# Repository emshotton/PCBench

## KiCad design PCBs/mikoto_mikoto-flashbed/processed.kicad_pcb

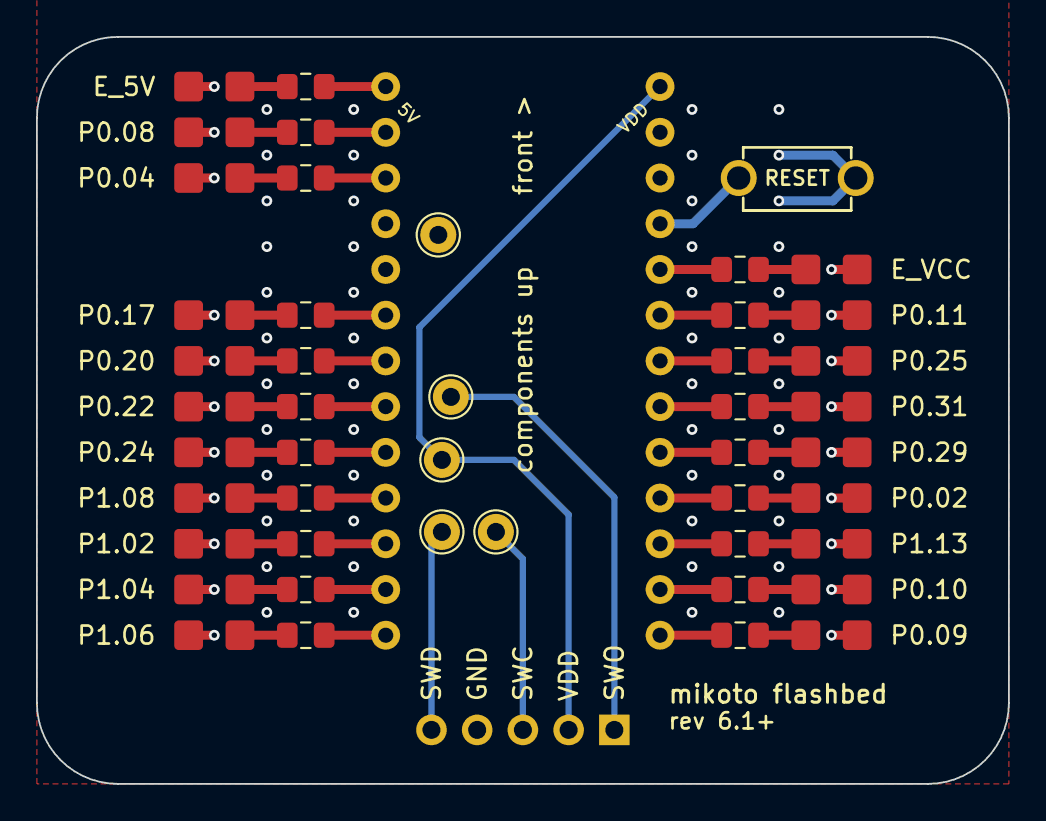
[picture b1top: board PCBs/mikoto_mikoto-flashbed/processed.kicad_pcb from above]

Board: 2 copper layers, 54.0 x 41.5 mm, 48 parts (1 on the bottom side), 46 nets.

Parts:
D1, D2, D3, D4, D5, D6, D7, D8, D9, D10, D11, D12, D13, D14, D15, D16, D17, D18, D19, D20: LED_Small; LED_1206_3216M_Castellated-nosilk
J1, J2, J3, J4, J5: Conn_01x01; TestPoint_THTPad_D2.0mm_Drill1.0mm
J7: Conn_01x05; PinHeader_1x05_P2.54mm_Horizontal
R1, R2, R3, R4, R5, R6, R7, R8, R9, R10, R11, R12, R13, R14, R15, R16, R17, R18, R19, R20: 2.2k; R_0805_2012Metric_Pad1.15x1.40mm_HandSolder
SW1: TVBP06; TACT_SWITCH_TVBP06
U1: mikoto-pins

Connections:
EXT_5V: R1.1, U1.1 (EXT_5V)
EXT_VCC: R20.1, U1.22 (VCC)
GND: D1.1 (K), D2.1 (K), D3.1 (K), D4.1 (K), D5.1 (K), D6.1 (K), D7.1 (K), D8.1 (K), D9.1 (K), D10.1 (K), D11.1 (K), D12.1 (K), D13.1 (K), D14.1 (K), D15.1 (K), D16.1 (K), D17.1 (K), D18.1 (K), D19.1 (K), D20.1 (K), J2.1, J7.4, SW1.2, U1.4 (GND), U1.5 (GND), U1.24 (GND)
unnamed: D1.2 (A), R1.2
unnamed: D2.2 (A), R2.2
unnamed: D3.2 (A), R3.2
unnamed: D4.2 (A), R4.2
unnamed: D5.2 (A), R5.2
unnamed: D6.2 (A), R6.2
unnamed: D7.2 (A), R7.2
unnamed: D8.2 (A), R8.2
unnamed: D9.2 (A), R9.2
unnamed: D10.2 (A), R10.2
unnamed: D11.2 (A), R11.2
unnamed: D12.2 (A), R12.2
unnamed: D13.2 (A), R13.2
unnamed: D14.2 (A), R14.2
unnamed: D15.2 (A), R15.2
unnamed: D16.2 (A), R16.2
unnamed: D17.2 (A), R17.2
unnamed: D18.2 (A), R18.2
unnamed: D19.2 (A), R19.2
unnamed: D20.2 (A), R20.2
P0.02: R15.1, U1.17
P0.04: R3.1, U1.3
P0.08: R2.1, U1.2
P0.09: R12.1, U1.14
P0.10: R13.1, U1.15
P0.11: R19.1, U1.21
P0.17: R4.1, U1.6
P0.20: R5.1, U1.7
P0.22: R6.1, U1.8
P0.24: R7.1, U1.9
P0.25: R18.1, U1.20
P0.29: R16.1, U1.18
P0.31: R17.1, U1.19
P1.02: R9.1, U1.11
P1.04: R10.1, U1.12
P1.06: R11.1, U1.13
P1.08: R8.1, U1.10
P1.13: R14.1, U1.16
RESET: SW1.1, U1.23 (RST)
SWC: J3.1, J7.3
SWD: J1.1, J7.5
SWO: J5.1, J7.1
VDD: J4.1, J7.2, U1.26 (VDD)

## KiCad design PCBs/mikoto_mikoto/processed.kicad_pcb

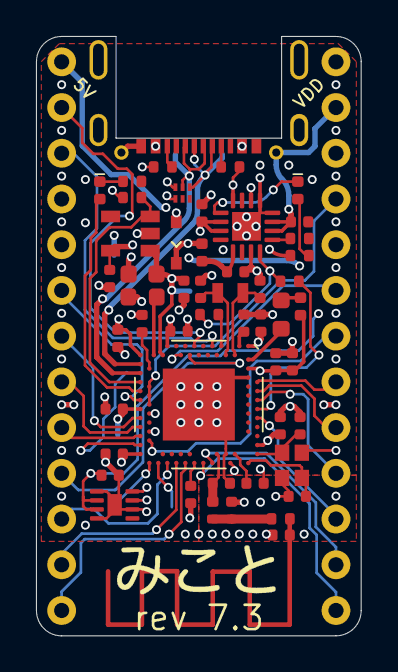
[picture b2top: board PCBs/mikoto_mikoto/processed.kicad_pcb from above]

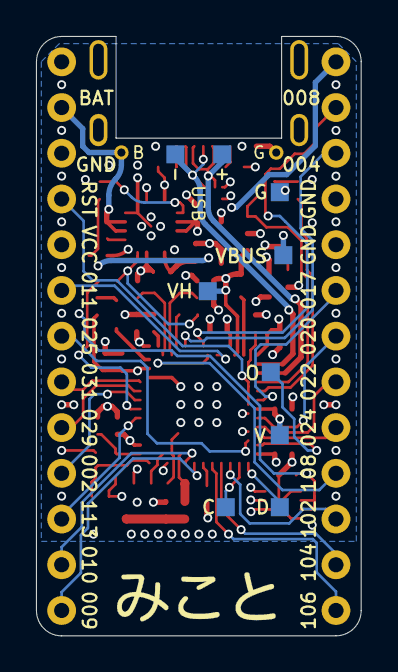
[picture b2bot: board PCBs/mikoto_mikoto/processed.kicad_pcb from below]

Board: 4 copper layers, 18.0 x 33.3 mm, 67 parts (10 on the bottom side), 61 nets.

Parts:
AE1: Antenna; 2.4GHz-meander-antenna-v2
C1, C13, C14, C20, C24, C25, C26: 4.7uF; Capacitor_0402_1005M-nosilk
C2, C3, C4, C10, C19: 100nF; Capacitor_0402_1005M-nosilk
C5, C9: 1pF; Capacitor_0402_1005M-nosilk
C6, C7, C17, C18: 15pF; Capacitor_0402_1005M-nosilk
C8, C15, C23: 1uF; Capacitor_0402_1005M-nosilk
C11: 100pF; Capacitor_0402_1005M-nosilk
C12: 1nF; Capacitor_0402_1005M-nosilk
C16: 47nF; Capacitor_0402_1005M-nosilk
C21: 10uF; Capacitor_0603_1608M-nosilk
C22: 1.5pF; Capacitor_0402_1005M-nosilk
D1: BLUE; LED_0402_1005Metric-nosilk
D3: ORANGE; LED_0402_1005Metric-nosilk
D5: PMEG4010CEJ; D_SOD-323F-nosilk
DUMMY1: logo_front; mikoto-logo
DUMMY2: logo_back; mikoto-logo
F1: 500mA hold; Fuse_0402_1005Metric
J1: USB_C_Receptacle_USB2.0; USB-C_C168688
J4, J5: PTH; PTH-0.8_0.45mm
L1: 3.9nH; Inductor_0402_1005M-nosilk
L2: 15nH; Inductor_0402_1005M-nosilk
L3, L4: 10uH; Inductor_0603_1608M-nosilk
NT1: NetTie_2; net-tie-2-tiny
R1: 3.9k; Resistor_0402_1005M-nosilk
R2: 2M; Resistor_0402_1005M-nosilk
R5: 1.5k; Resistor_0402_1005M-nosilk
R6, R7, R8: 10k; Resistor_0402_1005M-nosilk
R9, R10: 5.1k; Resistor_0402_1005M-nosilk
R11: 0R; Resistor_0402_1005M-nosilk
TP1, TP2, TP3, TP4, TP5, TP6, TP7, TP8, TP9: PAD; TestPoint_Pad_1.0x1.0mm-nosilk
U1: nRF52840; AQFN-73-1EP_7x7mm_P0.5mm_NRF52840-custom
U2: BQ24075RGT; VQFN-16-1EP_3x3mm_P0.5mm_EP1.6x1.6mm
U3: XC6220B331MR; SOT-23-5
U4: mikoto-pins
U5: ESDR0502NMUTAG; UDFN-6_1.2x1.0mm_P0.4mm
U6: MAX17048; TDFN-8-1EP_2x2mm_P0.5mm_EP0.8x1.2mm
Y1: 32MHz; Crystal_SMD_2016-4Pin_2.0x1.6mm
Y2: 32.768 kHz; Crystal_SMD_2012-2Pin_2.0x1.2mm

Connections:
/ANT: AE1.1 (A), C22.2, R11.2
/CC1: J1.A5 (CC1), R9.1
/CC2: J1.B5 (CC2), R10.1
BAT_I2C_SCL: U1.AC15 (P0.19), U6.7 (SCL)
BAT_I2C_SDA: U1.AC19 (P0.23), U6.8 (SDA)
BLUE_LED: D1.2 (A), U1.AD10 (P0.15)
CHARGE_CTRL_1: R7.1, U1.G1 (P0.26)
CHARGE_CTRL_2: R1.2, U1.A14 (P1.15)
EXT_5V: D5.1 (K), F1.2, U4.1 (EXT_5V)
GND: C1.1, C2.1, C3.1, C4.1, C5.1, C6.2, C7.2, C8.1, C10.2, C11.2, C12.2, C13.2, C14.1, C15.1, C16.1, C17.1, C18.1, C19.1, C20.1, C21.1, C22.1, C23.2, C24.1, C25.1, C26.1, J1.A1 (GND), J5.1, NT1.2, R2.2, R5.1, R8.2, R9.2, R10.2, TP5.1, U1.B7 (VSS), U1.EP (VSS), U2.4 (~CE), U2.5 (EN2), U2.8 (VSS), U2.15 (SYSOFF), U2.17 (VSS), U3.2 (GND), U4.4 (GND), U4.5 (GND), U4.24 (GND), U5.1 (GND), U6.1 (CTG), U6.4 (GND), U6.6 (QSTRT), U6.9 (EP), Y1.2, Y1.4
unnamed: C5.2, L1.1, R11.1
unnamed: D1.1 (K), R5.2
unnamed: D3.2 (A), R6.2
unnamed: D3.1 (K), U2.9 (~CHG)
unnamed: L2.2, L3.1
unnamed: C9.2, L1.2, U1.H23 (ANT)
unnamed: L3.2, U1.B3 (DCC)
unnamed: L4.2, U1.AB2 (DCCH)
unnamed: C10.1, U1.C1 (DEC1)
unnamed: C11.1, U1.D23 (DEC3)
unnamed: C15.2, C16.2, L2.1, U1.B5 (DEC4), U1.E24 (DEC6)
unnamed: C12.1, U1.N24 (DEC5)
unnamed: C13.1, U1.AC5 (DECUSB)
unnamed: C6.1, U1.B24 (XC1), Y1.1
unnamed: C7.1, U1.A23 (XC2), Y1.3
unnamed: C17.2, U1.D2 (XL1/P0.00), Y2.1
unnamed: C18.2, U1.F2 (XL2/P0.01), Y2.2
unnamed: C23.1, F1.1, U2.13 (IN)
unnamed: R1.1, R7.2, U2.16 (ISET)
unnamed: R8.1, U2.1 (TS)
P0.02: U1.A12 (AIN0/P0.02), U4.17
P0.04: U1.J1 (AIN2/P0.04), U4.3
P0.08: U1.N1 (P0.08), U4.2
P0.09: U1.L24 (NFC1/P0.09), U4.14
P0.10: U1.J24 (NFC2/P0.10), U4.15
P0.11: U1.T2 (TRACEDATA2/P0.11), U4.21
P0.17: U1.AD12 (P0.17), U4.6
P0.20: U1.AD16 (P0.20), U4.7
P0.22: U1.AD18 (P0.22), U4.8
P0.24: U1.AD20 (P0.24), U4.9
P0.25: U1.AC21 (P0.25), U4.20
P0.29: U1.A10 (AIN5/P0.29), U4.18
P0.31: U1.A8 (AIN7/P0.31), U4.19
P1.02: U1.W24 (P1.02), U4.11
P1.04: U1.U24 (P1.04), U4.12
P1.06: U1.R24 (P1.06), U4.13
P1.08: U1.P2 (P1.08), U4.10
P1.13: U1.A16 (P1.13), U4.16
PPH_VCC: C20.2, U3.5 (VOUT), U4.22 (VCC)
PPH_VCC_CTRL: R2.1, U1.AD8 (P0.13), U3.3 (CE)
RESET: U1.AC9 (P0.14), U1.AC11 (P0.16), U1.AC13 (P0.18/~RESET), U4.23 (RST)
SWC: TP1.1, U1.AA24 (SWDCLK)
SWD: TP2.1, U1.AC24 (SWDIO)
SWO: TP9.1, U1.AD22 (TRACEDATA0/P1.00)
USB_D+: J1.A6 (D+), J1.B6 (D+), TP6.1, U1.AD6 (D+), U5.5 (D+)
USB_D-: J1.A7 (D-), J1.B7 (D-), TP4.1, U1.AD4 (D-), U5.4 (D-)
VBAT: C19.2, C26.2, J4.1, U2.2 (BAT), U2.3 (BAT), U4.25 (RAW), U6.2 (CELL), U6.3 (VDD)
VBUS: C14.2, D5.2 (A), J1.A4 (VBUS), TP8.1, U1.AD2 (VBUS), U5.6 (VBUS)
VDDH: C21.2, C24.2, C25.2, R6.1, TP7.1, U1.Y2 (VDDH), U2.6 (EN1), U2.10 (OUT), U2.11 (OUT), U3.1 (VIN)
VDD_NRF: C1.2, C2.2, C3.2, C4.2, C8.2, L4.1, TP3.1, U1.A22 (VDD), U1.AD14 (VDD), U1.AD23 (VDD), U1.B1 (VDD), U1.W1 (VDD), U4.26 (VDD)
VSS_PA: C9.1, NT1.1, U1.F23 (VSS_PA)

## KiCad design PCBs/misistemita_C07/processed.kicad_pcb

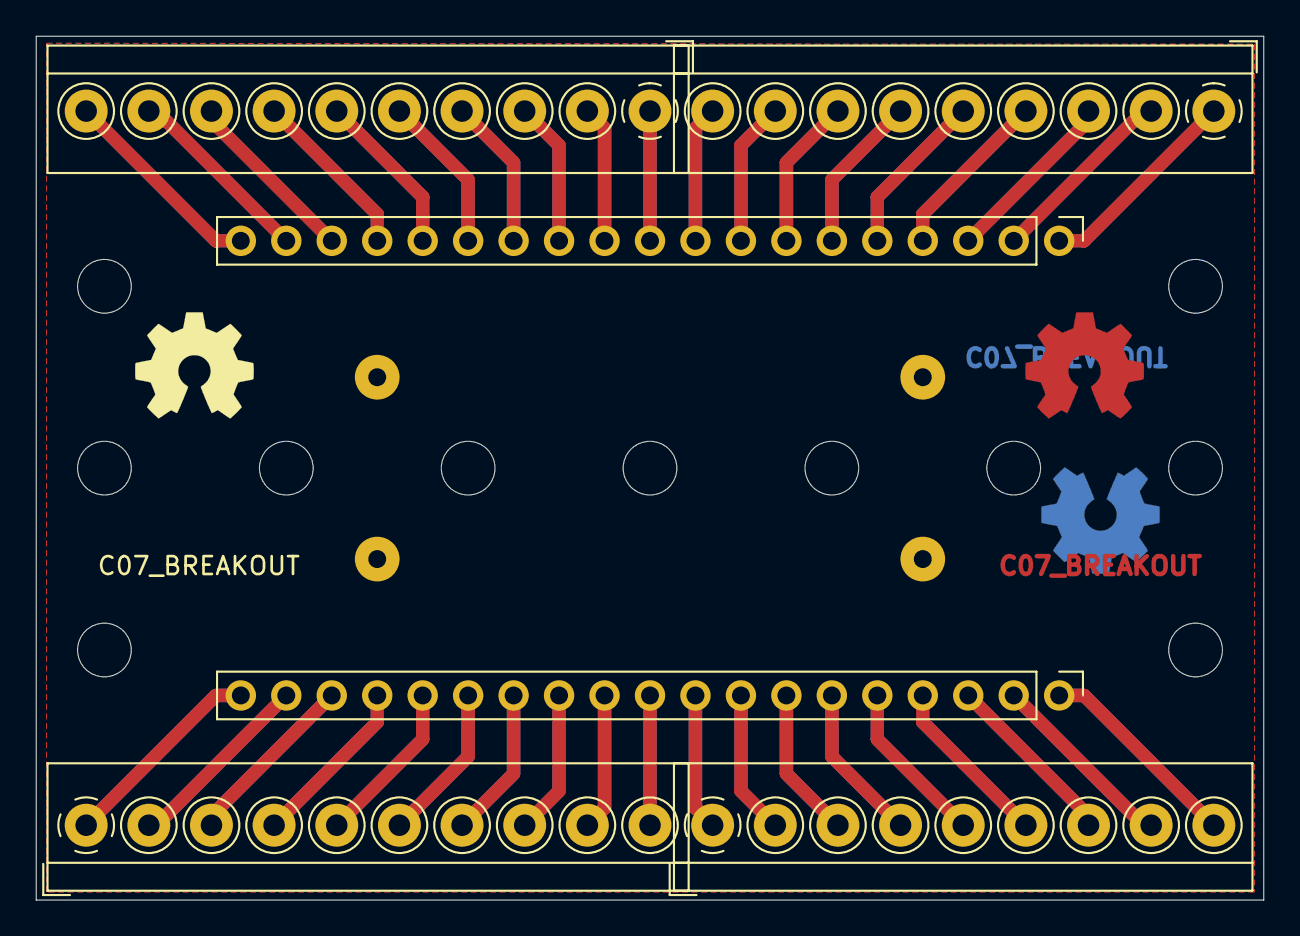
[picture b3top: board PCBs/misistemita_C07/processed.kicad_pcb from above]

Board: 2 copper layers, 68.6 x 48.3 mm, 21 parts (0 on the bottom side), 39 nets.

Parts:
HB0, HB6: MountingHole; MountingHole_3mm
HC0, HC1, HC2, HC3, HC4, HC5, HC6: MountingHole; MountingHole_3mm
HD0, HD6: MountingHole; MountingHole_3mm
J0, J1, J2, J3: Conn_01x01_Male; SolderWirePad_1x01_Drill1mm
J4, J6: Conn_01x10_Female; TerminalBlock_4Ucon_1x10_P3.50mm_Horizontal
J5, J7: Conn_01x09_Female; TerminalBlock_4Ucon_1x09_P3.50mm_Horizontal
J8, J9: Conn_01x19_Female; PinHeader_1x19_P2.54mm_Vertical

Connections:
unnamed: J0.1, J1.1, J2.1, J3.1
unnamed: J4.1, J8.10
unnamed: J4.2, J8.11
unnamed: J4.3, J8.12
unnamed: J4.4, J8.13
unnamed: J4.5, J8.14
unnamed: J4.6, J8.15
unnamed: J4.7, J8.16
unnamed: J4.8, J8.17
unnamed: J4.9, J8.18
unnamed: J4.10, J8.19
unnamed: J5.1, J8.1
unnamed: J5.2, J8.2
unnamed: J5.3, J8.3
unnamed: J5.4, J8.4
unnamed: J5.5, J8.5
unnamed: J5.6, J8.6
unnamed: J5.7, J8.7
unnamed: J5.8, J8.8
unnamed: J5.9, J8.9
unnamed: J6.1, J9.19
unnamed: J6.2, J9.18
unnamed: J6.3, J9.17
unnamed: J6.4, J9.16
unnamed: J6.5, J9.15
unnamed: J6.6, J9.14
unnamed: J6.7, J9.13
unnamed: J6.8, J9.12
unnamed: J6.9, J9.11
unnamed: J6.10, J9.10
unnamed: J7.1, J9.9
unnamed: J7.2, J9.8
unnamed: J7.3, J9.7
unnamed: J7.4, J9.6
unnamed: J7.5, J9.5
unnamed: J7.6, J9.4
unnamed: J7.7, J9.3
unnamed: J7.8, J9.2
unnamed: J7.9, J9.1

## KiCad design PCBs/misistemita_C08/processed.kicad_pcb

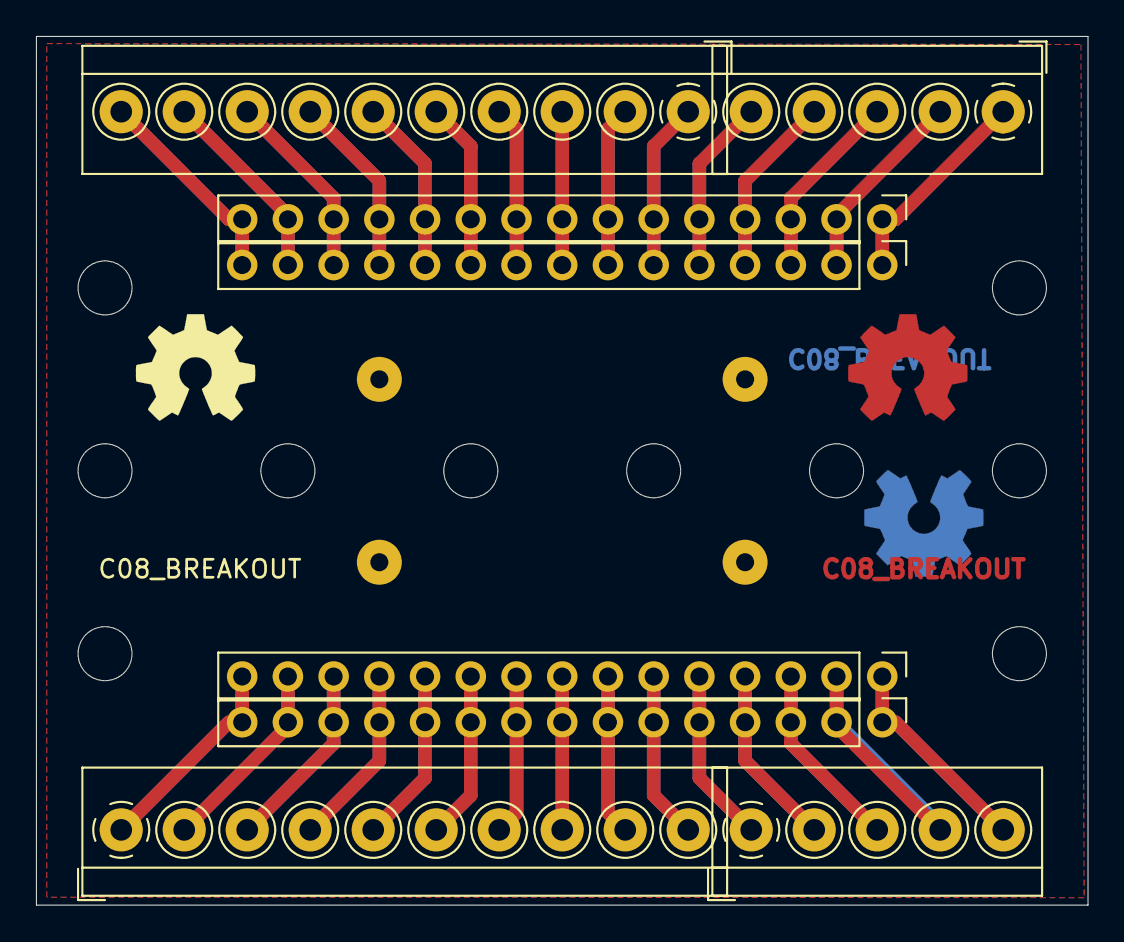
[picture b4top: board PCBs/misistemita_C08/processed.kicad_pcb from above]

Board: 2 copper layers, 58.4 x 48.3 mm, 22 parts (0 on the bottom side), 31 nets.

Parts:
HB0, HB6: MountingHole; MountingHole_3mm
HC0, HC1, HC2, HC3, HC4, HC5: MountingHole; MountingHole_3mm
HD0, HD6: MountingHole; MountingHole_3mm
J0, J1, J2, J3: Conn_01x01_Male; SolderWirePad_1x01_Drill1mm
J4, J6: Conn_01x10_Female; TerminalBlock_4Ucon_1x10_P3.50mm_Horizontal
J5, J7: Conn_01x05_Female; TerminalBlock_4Ucon_1x05_P3.50mm_Horizontal
J8, J9, J10, J11: Conn_01x15_Female; PinHeader_1x15_P2.54mm_Vertical

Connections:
unnamed: J0.1, J1.1, J2.1, J3.1
unnamed: J5.1, J8.1, J10.1
unnamed: J5.2, J8.2, J10.2
unnamed: J5.3, J8.3, J10.3
unnamed: J5.4, J8.4, J10.4
unnamed: J5.5, J8.5, J10.5
unnamed: J4.1, J8.6, J10.6
unnamed: J4.2, J8.7, J10.7
unnamed: J4.3, J8.8, J10.8
unnamed: J4.4, J8.9, J10.9
unnamed: J4.5, J8.10, J10.10
unnamed: J4.6, J8.11, J10.11
unnamed: J4.7, J8.12, J10.12
unnamed: J4.8, J8.13, J10.13
unnamed: J4.9, J8.14, J10.14
unnamed: J4.10, J8.15, J10.15
unnamed: J7.5, J9.1, J11.1
unnamed: J7.4, J9.2, J11.2
unnamed: J7.3, J9.3, J11.3
unnamed: J7.2, J9.4, J11.4
unnamed: J7.1, J9.5, J11.5
unnamed: J6.10, J9.6, J11.6
unnamed: J6.9, J9.7, J11.7
unnamed: J6.8, J9.8, J11.8
unnamed: J6.7, J9.9, J11.9
unnamed: J6.6, J9.10, J11.10
unnamed: J6.5, J9.11, J11.11
unnamed: J6.4, J9.12, J11.12
unnamed: J6.3, J9.13, J11.13
unnamed: J6.2, J9.14, J11.14
unnamed: J6.1, J9.15, J11.15

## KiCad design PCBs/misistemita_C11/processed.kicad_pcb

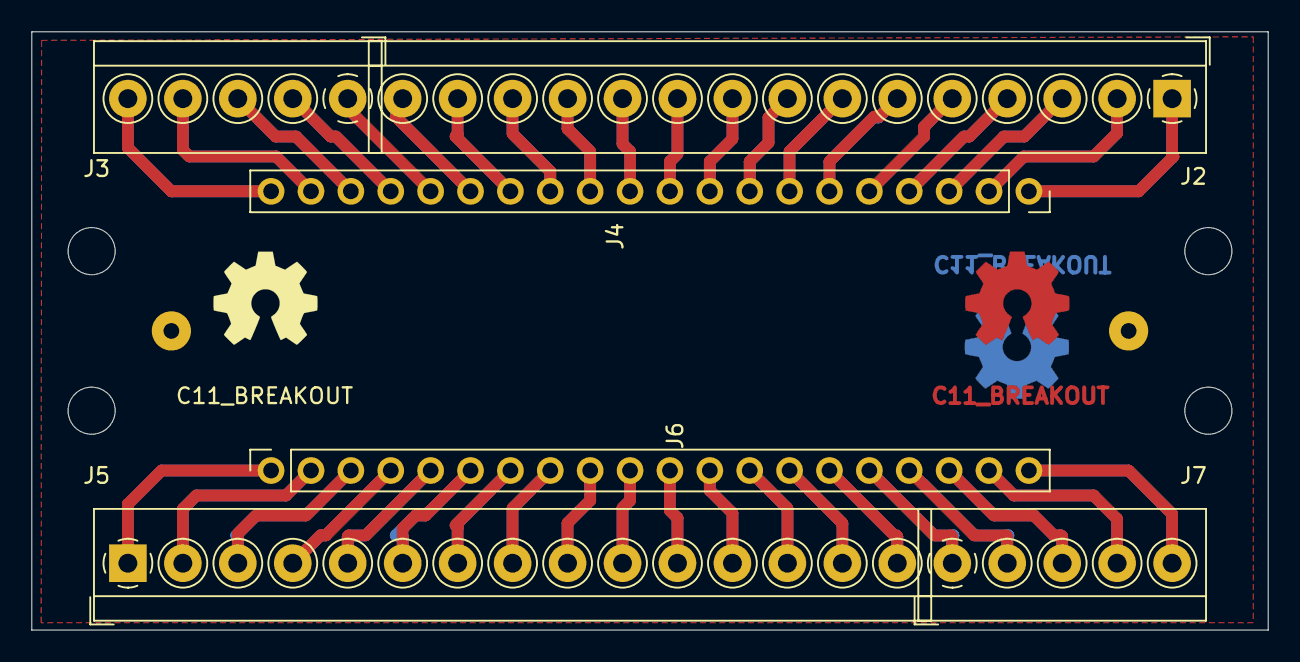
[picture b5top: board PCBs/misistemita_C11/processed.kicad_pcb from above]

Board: 2 copper layers, 78.7 x 38.1 mm, 12 parts (0 on the bottom side), 41 nets.

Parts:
HB0, HB5: MountingHole; MountingHole_3mm
HC0, HC5: MountingHole; MountingHole_3mm
J0, J1: Conn_01x01_Male; SolderWirePad_1x01_Drill1mm
J2, J5: Conn_01x15_Female; TerminalBlock_4Ucon_1x15_P3.50mm_Horizontal
J3, J7: Conn_01x05_Female; TerminalBlock_4Ucon_1x05_P3.50mm_Horizontal
J4, J6: Conn_01x20_Female; PinSocket_1x20_P2.54mm_Vertical

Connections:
unnamed: J0.1, J1.1
unnamed: J2.1, J4.1
unnamed: J2.2, J4.2
unnamed: J2.3, J4.3
unnamed: J2.4, J4.4
unnamed: J2.5, J4.5
unnamed: J2.6, J4.6
unnamed: J2.7, J4.7
unnamed: J2.8, J4.8
unnamed: J2.9, J4.9
unnamed: J2.10, J4.10
unnamed: J2.11, J4.11
unnamed: J2.12, J4.12
unnamed: J2.13, J4.13
unnamed: J2.14, J4.14
unnamed: J2.15, J4.15
unnamed: J3.1, J4.16
unnamed: J3.2, J4.17
unnamed: J3.3, J4.18
unnamed: J3.4, J4.19
unnamed: J3.5, J4.20
unnamed: J5.1, J6.1
unnamed: J5.2, J6.2
unnamed: J5.3, J6.3
unnamed: J5.4, J6.4
unnamed: J5.5, J6.5
unnamed: J5.6, J6.6
unnamed: J5.7, J6.7
unnamed: J5.8, J6.8
unnamed: J5.9, J6.9
unnamed: J5.10, J6.10
unnamed: J5.11, J6.11
unnamed: J5.12, J6.12
unnamed: J5.13, J6.13
unnamed: J5.14, J6.14
unnamed: J5.15, J6.15
unnamed: J6.16, J7.1
unnamed: J6.17, J7.2
unnamed: J6.18, J7.3
unnamed: J6.19, J7.4
unnamed: J6.20, J7.5

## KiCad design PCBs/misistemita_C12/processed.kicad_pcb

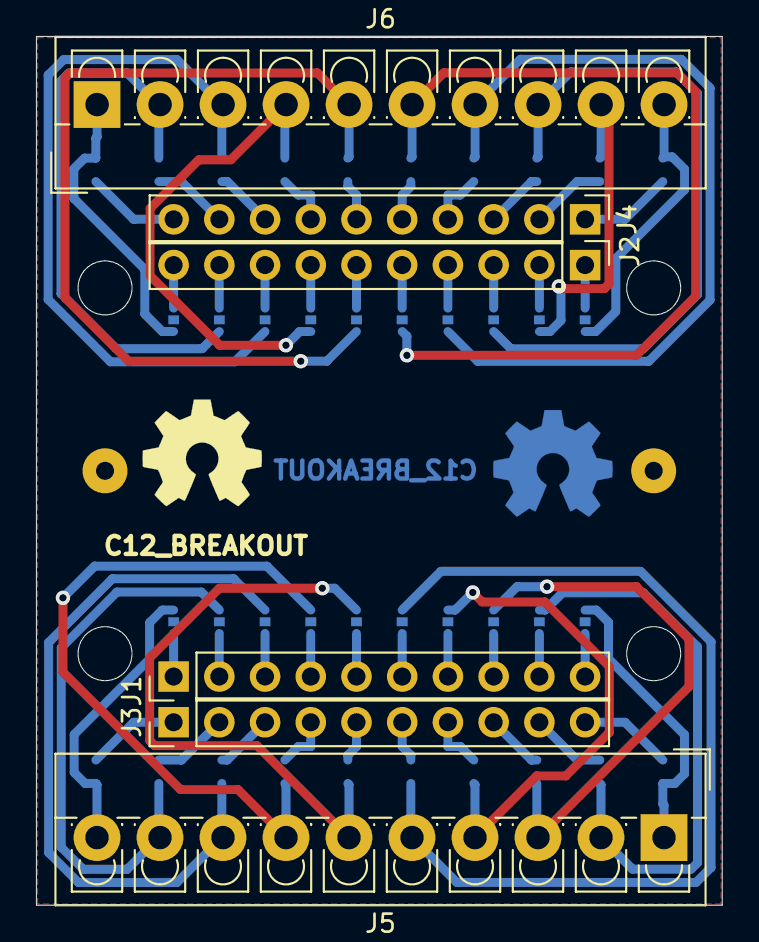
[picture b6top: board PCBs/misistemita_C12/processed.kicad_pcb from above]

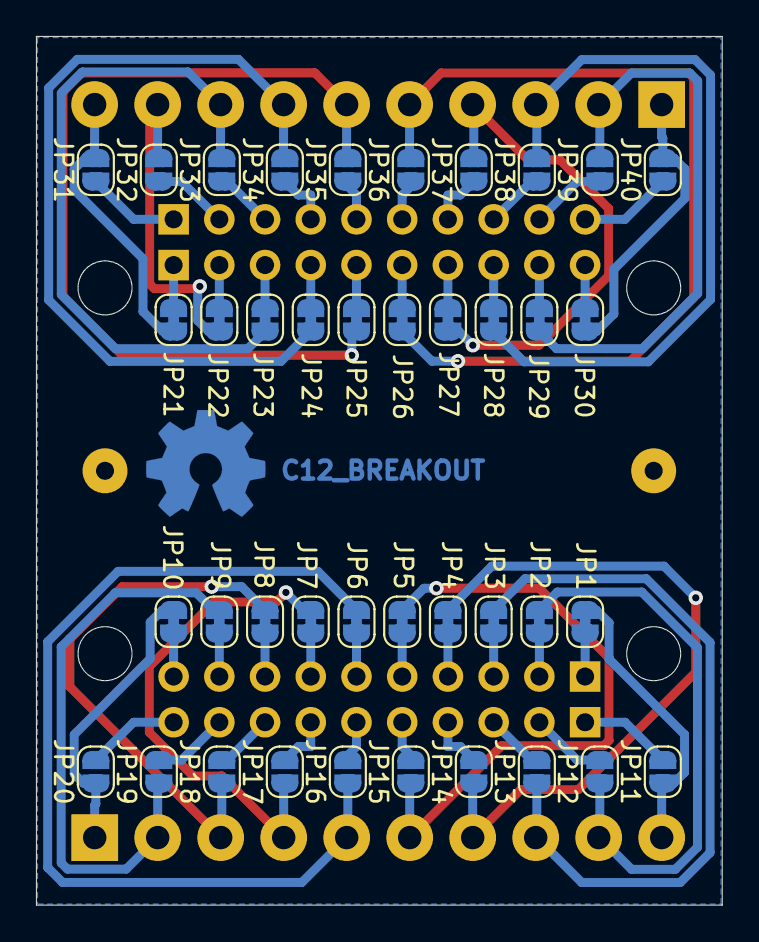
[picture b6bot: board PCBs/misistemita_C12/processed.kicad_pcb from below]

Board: 2 copper layers, 38.1 x 48.3 mm, 54 parts (41 on the bottom side), 61 nets.

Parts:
HB0, HB3: MountingHole; MountingHole_3mm
HD0, HD3: MountingHole; MountingHole_3mm
J1, J2, J3, J4: Conn_01x10_Female; PinHeader_1x10_P2.54mm_Vertical
J5, J6: Conn_01x10_Female; TerminalBlock_4Ucon_1x10_P3.50mm_Vertical
J10, J11: Conn_01x01_Male; SolderWirePad_1x01_Drill1mm
JP1, JP2, JP3, JP4, JP5, JP6, JP7, JP8, JP9, JP10, JP21, JP22, JP23, JP24, JP25, JP26, JP27, JP28, JP29, JP30: SolderJumper_2_Bridged; SolderJumper-2_P1.3mm_Bridged_RoundedPad1.0x1.5mm
JP11, JP12, JP13, JP14, JP15, JP16, JP17, JP18, JP19, JP20, JP31, JP32, JP33, JP34, JP35, JP36, JP37, JP38, JP39, JP40: SolderJumper_2_Open; SolderJumper-2_P1.3mm_Open_RoundedPad1.0x1.5mm
REFS0**: OSHW-Symbol_6.7x6mm_Copper
REFS1**: OSHW-Symbol_6.7x6mm_SilkScreen

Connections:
unnamed: J1.1, JP1.2 (B)
unnamed: J1.2, JP2.2 (B)
unnamed: J1.3, JP3.2 (B)
unnamed: J1.4, JP4.2 (B)
unnamed: J1.5, JP5.2 (B)
unnamed: J1.6, JP6.2 (B)
unnamed: J1.7, JP7.2 (B)
unnamed: J1.8, JP8.2 (B)
unnamed: J1.9, JP9.2 (B)
unnamed: J1.10, JP10.2 (B)
unnamed: J2.1, JP21.1 (A)
unnamed: J2.2, JP22.1 (A)
unnamed: J2.3, JP23.1 (A)
unnamed: J2.4, JP24.1 (A)
unnamed: J2.5, JP25.1 (A)
unnamed: J2.6, JP26.1 (A)
unnamed: J2.7, JP27.1 (A)
unnamed: J2.8, JP28.1 (A)
unnamed: J2.9, JP29.1 (A)
unnamed: J2.10, JP30.1 (A)
unnamed: J3.1, JP11.2 (B)
unnamed: J3.2, JP12.2 (B)
unnamed: J3.3, JP13.2 (B)
unnamed: J3.4, JP14.2 (B)
unnamed: J3.5, JP15.2 (B)
unnamed: J3.6, JP16.2 (B)
unnamed: J3.7, JP17.2 (B)
unnamed: J3.8, JP18.2 (B)
unnamed: J3.9, JP19.2 (B)
unnamed: J3.10, JP20.2 (B)
unnamed: J4.1, JP31.1 (A)
unnamed: J4.2, JP32.1 (A)
unnamed: J4.3, JP33.1 (A)
unnamed: J4.4, JP34.1 (A)
unnamed: J4.5, JP35.1 (A)
unnamed: J4.6, JP36.1 (A)
unnamed: J4.7, JP37.1 (A)
unnamed: J4.8, JP38.1 (A)
unnamed: J4.9, JP39.1 (A)
unnamed: J4.10, JP40.1 (A)
unnamed: J10.1, J11.1
unnamed: J5.10, JP1.1 (A), JP11.1 (A)
unnamed: J5.1, JP10.1 (A), JP20.1 (A)
unnamed: J5.9, JP2.1 (A), JP12.1 (A)
unnamed: J5.8, JP3.1 (A), JP13.1 (A)
unnamed: J5.7, JP4.1 (A), JP14.1 (A)
unnamed: J5.6, JP5.1 (A), JP15.1 (A)
unnamed: J5.5, JP6.1 (A), JP16.1 (A)
unnamed: J5.4, JP7.1 (A), JP17.1 (A)
unnamed: J5.3, JP8.1 (A), JP18.1 (A)
unnamed: J5.2, JP9.1 (A), JP19.1 (A)
unnamed: J6.10, JP21.2 (B), JP31.2 (B)
unnamed: J6.9, JP22.2 (B), JP32.2 (B)
unnamed: J6.8, JP23.2 (B), JP33.2 (B)
unnamed: J6.7, JP24.2 (B), JP34.2 (B)
unnamed: J6.6, JP25.2 (B), JP35.2 (B)
unnamed: J6.5, JP26.2 (B), JP36.2 (B)
unnamed: J6.4, JP27.2 (B), JP37.2 (B)
unnamed: J6.3, JP28.2 (B), JP38.2 (B)
unnamed: J6.2, JP29.2 (B), JP39.2 (B)
unnamed: J6.1, JP30.2 (B), JP40.2 (B)
